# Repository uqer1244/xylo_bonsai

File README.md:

# xylo_bonsai

36key split with zmk + promicro nicenano v2 compatiablilty, LP

- LP
- wireless (BLE)
- affordable price
- handy

## To-Do
- led indicator
- better USB-C port location
- preciese case building

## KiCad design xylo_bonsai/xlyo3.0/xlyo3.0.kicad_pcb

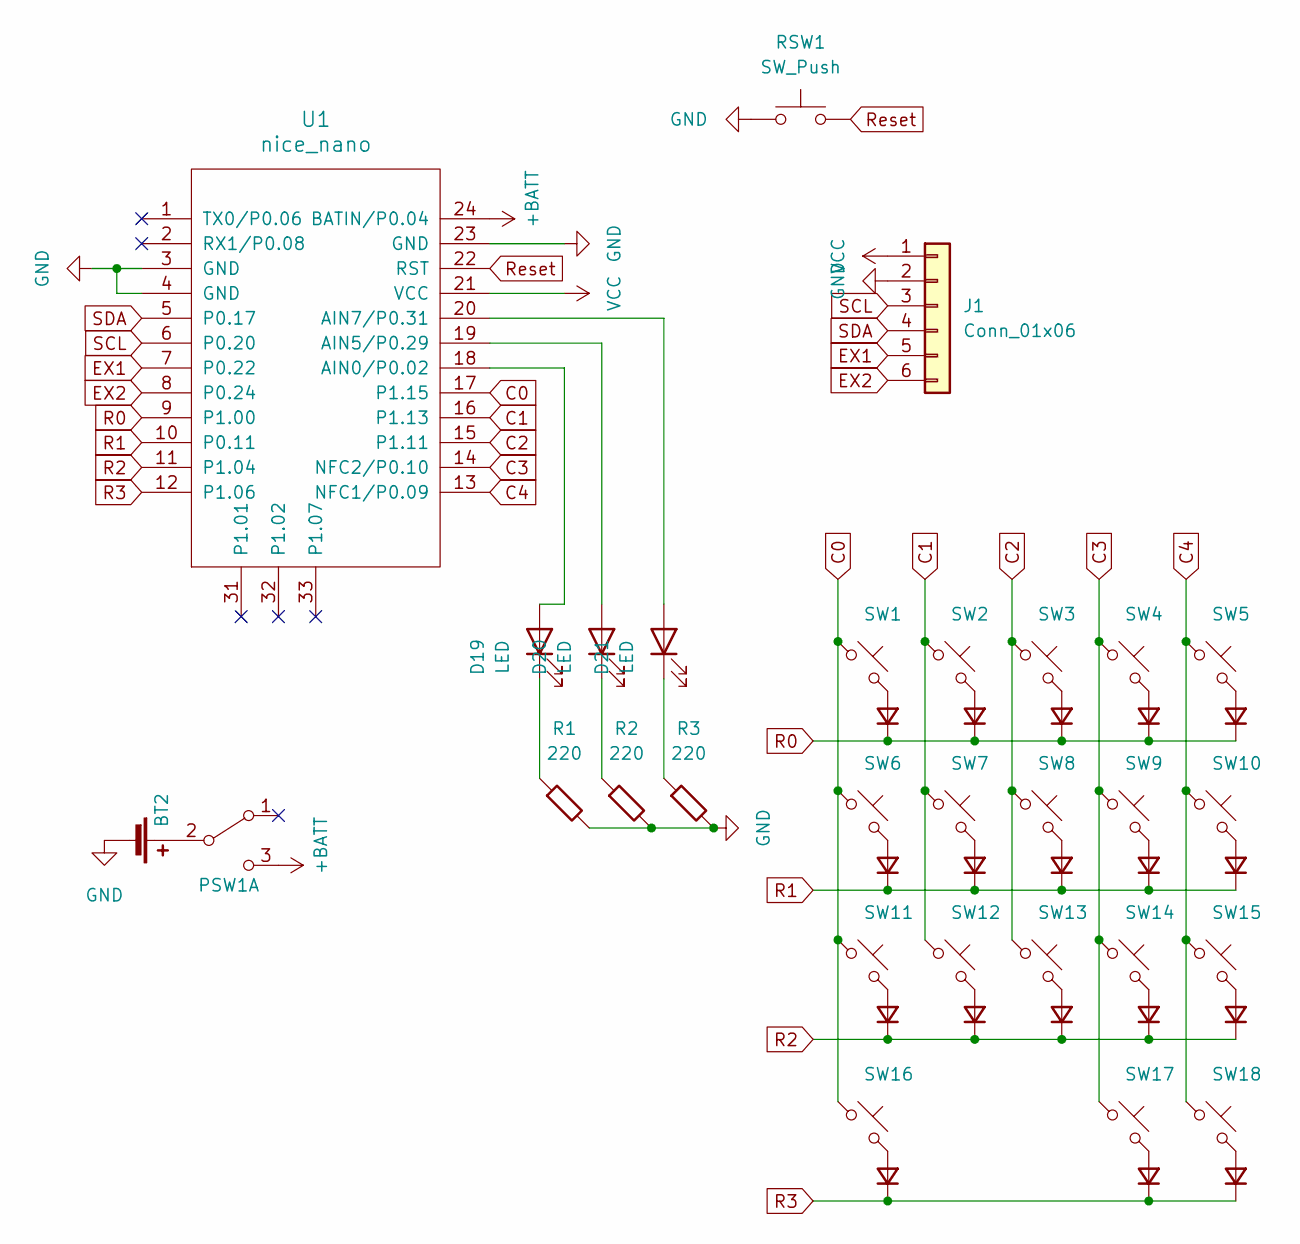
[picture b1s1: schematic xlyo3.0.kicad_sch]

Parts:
BT2: Battery_Cell; Battery_TH
D1, D2, D3, D4, D5, D6, D7, D8, D9, D10, D11, D12, D13, D14, D15, D16, D17, D18: D_Small; D3_TH_SMD_v2
D19, D20, D21: LED; LED_3mm_reversible
J1: Conn_01x06; PinHeader_1x06_P2.00mm_Vertical
PSW1: SW_DPDT_x2; MSK12C02_reversible
R1, R2, R3: 220; R_1206_DoubleSided
RSW1: SW_Push; ResetSW
SW1, SW2, SW3, SW4, SW5, SW6, SW7, SW8, SW9, SW10, SW11, SW12, SW13, SW14, SW15, SW16, SW17, SW18: MX_SW_HS; SW_Hotswap_Kailh_Choc_V1V2_rev
U1: nice_nano; ProMicro_jumpers

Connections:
+BATT: PSW1.3 (C), U1.24 (BATIN/P0.04)
C0: SW1.1, SW6.1, SW11.1, SW16.1, U1.17 (P1.15)
C1: SW2.1, SW7.1, SW12.1, U1.16 (P1.13)
C2: SW3.1, SW8.1, SW13.1, U1.15 (P1.11)
C3: SW4.1, SW9.1, SW14.1, SW17.1, U1.14 (NFC2/P0.10)
C4: SW5.1, SW10.1, SW15.1, SW18.1, U1.13 (NFC1/P0.09)
EX1: J1.5, U1.7 (P0.22)
EX2: J1.6, U1.8 (P0.24)
GND: BT2.2 (-), J1.2, R1.2, R2.2, R3.2, RSW1.1, U1.3 (GND), U1.4 (GND), U1.23 (GND)
unnamed: BT2.1 (+), PSW1.2 (B)
unnamed: D1.2 (A), SW1.2
unnamed: D2.2 (A), SW2.2
unnamed: D3.2 (A), SW3.2
unnamed: D4.2 (A), SW4.2
unnamed: D5.2 (A), SW5.2
unnamed: D6.2 (A), SW6.2
unnamed: D7.2 (A), SW7.2
unnamed: D8.2 (A), SW8.2
unnamed: D9.2 (A), SW9.2
unnamed: D10.2 (A), SW10.2
unnamed: D11.2 (A), SW11.2
unnamed: D12.2 (A), SW12.2
unnamed: D13.2 (A), SW13.2
unnamed: D14.2 (A), SW14.2
unnamed: D15.2 (A), SW15.2
unnamed: D16.2 (A), SW16.2
unnamed: D17.2 (A), SW17.2
unnamed: D18.2 (A), SW18.2
unnamed: D19.2 (A), U1.18 (AIN0/P0.02)
unnamed: D19.1 (K), R1.1
unnamed: D20.2 (A), U1.19 (AIN5/P0.29)
unnamed: D20.1 (K), R2.1
unnamed: D21.2 (A), U1.20 (AIN7/P0.31)
unnamed: D21.1 (K), R3.1
R0: D1.1 (K), D2.1 (K), D3.1 (K), D4.1 (K), D5.1 (K), U1.9 (P1.00)
R1: D6.1 (K), D7.1 (K), D8.1 (K), D9.1 (K), D10.1 (K), U1.10 (P0.11)
R2: D11.1 (K), D12.1 (K), D13.1 (K), D14.1 (K), D15.1 (K), U1.11 (P1.04)
R3: D16.1 (K), D17.1 (K), D18.1 (K), U1.12 (P1.06)
Reset: RSW1.2, U1.22 (RST)
SCL: J1.3, U1.6 (P0.20)
SDA: J1.4, U1.5 (P0.17)
VCC: J1.1, U1.21 (VCC)

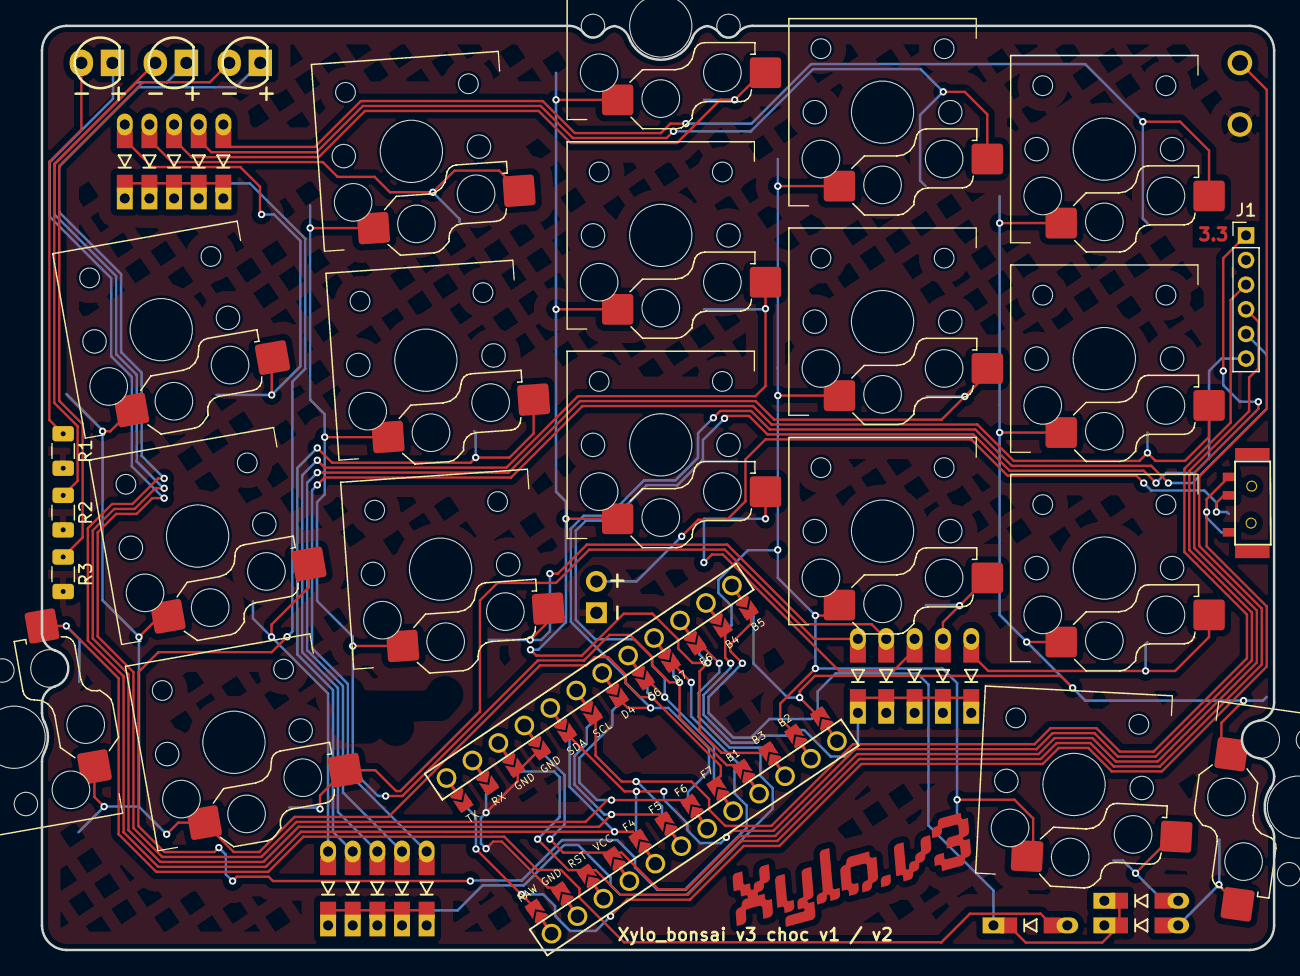
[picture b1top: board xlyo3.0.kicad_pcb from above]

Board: 2 copper layers, 100.0 x 75.0 mm, 47 parts (0 on the bottom side), 42 nets.

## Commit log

2025-06-12 init
2025-06-12 add .ai
2025-07-13 add 3dp case
2025-07-13 add 3dp case,,,
2025-08-28 v3 update! with better promicro position + 6pin (P2.00) EXpins for haptic / OLED / extra switch mods
